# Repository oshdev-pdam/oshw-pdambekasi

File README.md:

# oshw-pdambekasi

Repositori rintisan untuk OSH Development sensor tekanan air untuk PDAM Kota Bekasi

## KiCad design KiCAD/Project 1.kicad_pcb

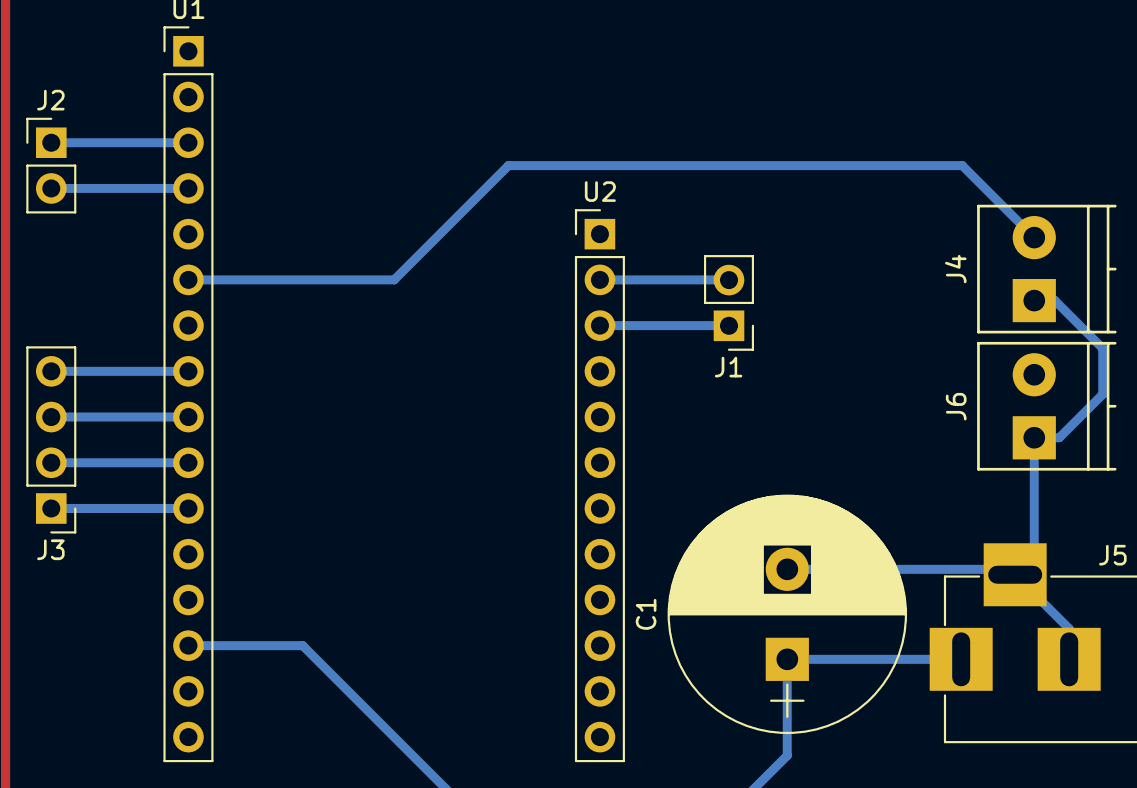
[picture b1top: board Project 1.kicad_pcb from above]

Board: 2 copper layers, 9 parts (0 on the bottom side), 11 nets.

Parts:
C1: CAP_POL; CP_Radial_D13.0mm_P5.00mm
J1: SIM900; Pin_Header_Straight_1x02_Pitch2.54mm
J2: RTC; Pin_Header_Straight_1x02_Pitch2.54mm
J3: Micro Pro; Pin_Header_Straight_1x04_Pitch2.54mm
J4: solid state controller; TerminalBlock_Phoenix_PT-3.5mm_2pol
J5: Jack-DC; BARREL_JACK
J6: Battery; TerminalBlock_Phoenix_PT-3.5mm_2pol
U1: ADAFRUIT_FEATHER; Pin_Header_Straight_1x16_Pitch2.54mm
U2: ADAFRUIT_FEATHER; Pin_Header_Straight_1x12_Pitch2.54mm

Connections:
DE: J3.2, U1.10
DI: J3.1, U1.11
GND: C1.2, J4.1, J5.2, J5.3, J6.1
RE: J3.3, U1.9
RO: J3.4, U1.8
RX: J1.2, U2.2
SCL: J2.2, U1.4
SDA: J2.1, U1.3
SS: J4.2, U1.6
TX: J1.1, U2.3
VCC: C1.1, J5.1, U1.14

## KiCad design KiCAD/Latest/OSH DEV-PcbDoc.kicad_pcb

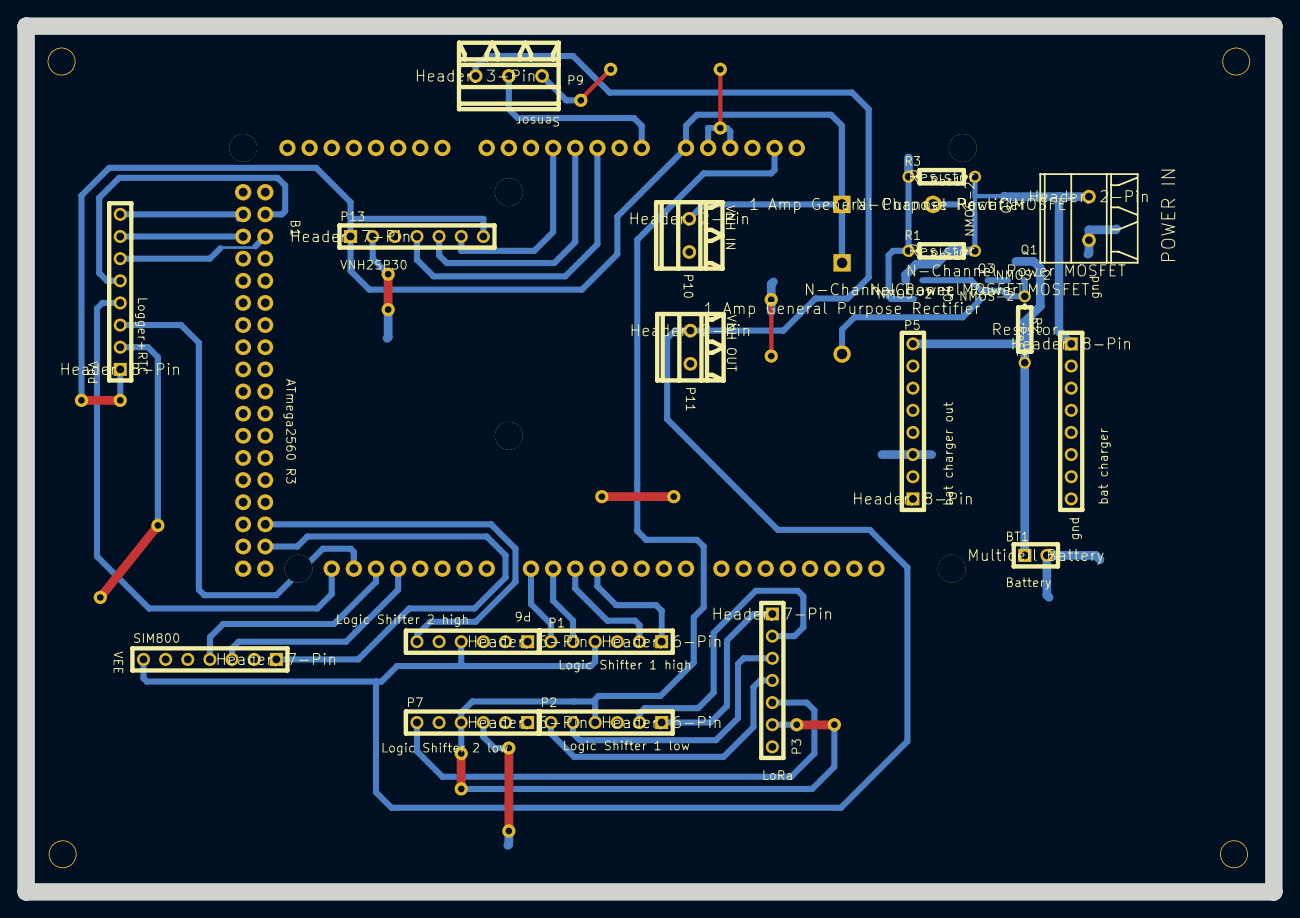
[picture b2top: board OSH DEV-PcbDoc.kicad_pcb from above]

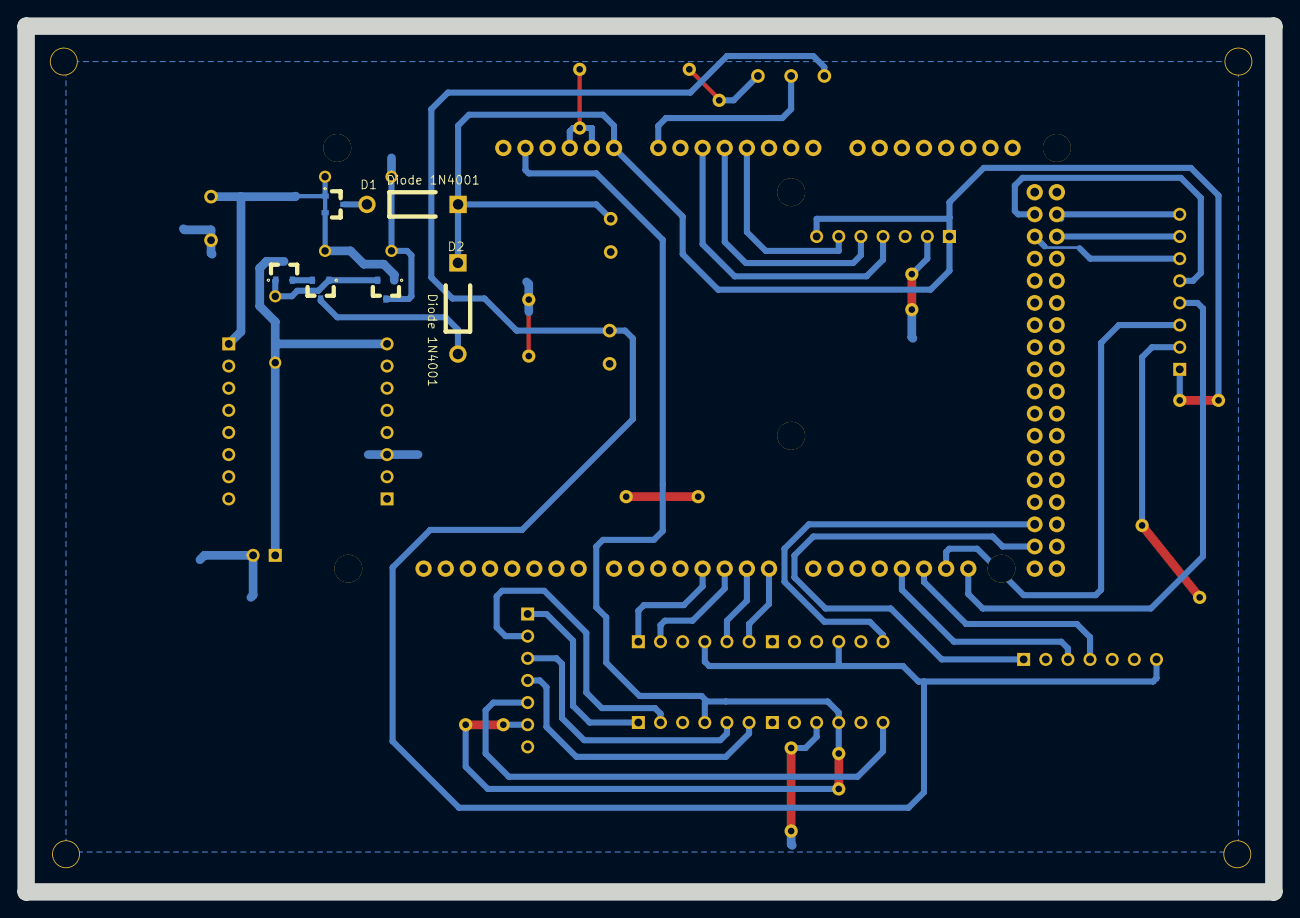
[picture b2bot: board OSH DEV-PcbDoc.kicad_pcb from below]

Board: 2 copper layers, 143.1 x 99.3 mm, 25 parts (6 on the bottom side), 33 nets.

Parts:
B1: ARDUINO_MEGA
BT1: Multicell Battery; BAT-2
D1, D2: 1 Amp General Purpose Rectifier; DO-41
P1, P2, P6, P7: Header, 6-Pin; HDR1X6
P3, P12, P13: Header, 7-Pin; HDR1X7
P4, P5, P14: Header, 8-Pin; HDR1X8
P8: Header, 2-Pin; MKDS3_2RMM
P9: Header, 3-Pin; MKDS1_3R3_8
P10, P11: Header, 2-Pin; MKDS1_2R3_8
Q1, Q2, Q3, Q4: N-Channel Power MOSFET; SOT-23B_L
R1, R2, R3: Resistor; AXIAL-0.3

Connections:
3.3: B1.3.3V, P2.4, P3.6, P7.4
GND: B1.GND@, BT1.2, P1.3, P2.3, P3.7, P4.6, P4.7, P4.8, P5.1, P5.2, P5.3, P6.3, P7.3, P8.2, P9.3, P10.2, P11.2, P12.6, P13.2, P14.2, Q4.3, R1.1, R3.1
NetB1_0: B1.0, P1.6
NetB1_1: B1.1, P1.5
NetB1_2: B1.2, P1.2
NetB1_3: B1.3, P1.1
NetB1_18: B1.18, P12.3
NetB1_19: B1.19, P12.4
NetB1_20: B1.20, P14.3
NetB1_21: B1.21, P14.4
NetB1_22: B1.22, P12.1
NetB1_24: B1.24, P6.6
NetB1_50: B1.50, P14.6
NetB1_51: B1.51, P14.7
NetB1_52: B1.52, P14.5
NetB1_53: B1.53, P14.8
NetB1_A0: B1.A0, P9.2
NetB1_A2: B1.A2, P13.4
NetB1_A3: B1.A3, P13.5
NetB1_A4: B1.A4, P13.6
NetD1_1: D1.1, Q2.3
NetD2_1: D2.1, Q3.3
NetP2_1: P2.1, P3.1
NetP2_2: P2.2, P3.2
NetP2_5: P2.5, P3.3
NetP2_6: P2.6, P3.4
NetP3_5: P3.5, P7.6
NetQ1_1: Q1.1, Q3.1, Q4.2, R2.1
NetQ1_2: Q1.2, Q3.2
VBAT: BT1.1, P5.8, Q1.3, R2.2
VDD: B1.VIN, D1.2, D2.2, P10.1, P13.1, P13.7, P14.1
VEE: P1.4, P6.4, P9.1, P11.1, P12.7
VIN: P4.1, P8.1, Q2.1, Q2.2, Q4.1, R1.2, R3.2

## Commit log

2017-10-12 Create Design
2017-10-12 reorganize repo
2017-10-12 merge
2017-10-17 Product Wireframe
    Representasi visual dari alur kerja alat, ditampilkan dalam dokumentasi secara deskriptif dan dengan bantuan berupa bagan
2017-10-19 Bill Of Material
    anggaran perbelanjaan dan link toko pembelian
2017-10-19 Add BOM Completion for Unit 1
2017-10-20 KiCAD files eeschema and pcb
2017-10-20 KiCAD
    KiCAD file seluruh design skematik (Eeschema) dan PCB
2017-10-20 KiCAD Files
    Eeschema dan PCB file electrical design
2017-10-30 KiCAD Files
    KiCAD files lengkap untuk design ver.1
2017-10-31 Basic Function Codes
    Master: Adafruit Feather M0
    Slave: Arduino Micro
2017-11-06 Full Code v1
2017-11-06 Conversion to VS2017 and add .gitignore
2017-11-19 Use FONA library with SIM800L
2017-12-28 2nd gen
    Code dev for 2nd generation module. No more slave
2018-01-17 Module v2 (Gateway)
2018-02-25 HTTP Data Send Update
    Now sending data through Adafruit.io's REST API
2018-02-25 Quota Check Update
    Added quota check, using USSD commands
2018-04-09 Latest PCB Design
2018-04-11 Latest Schematics
2018-04-12 Schematics PDF
2018-04-24 Data Gathering & Analysis
    Ambil data bulan Maret-April untuk unit 1, 2, 3. Program untuk mengkonversi data .json ke .csv (dan grafik penggunaan 24 jam) ada di file Data_Gathering.py
2018-07-15 v4
    Code with 10 minutes sleep time
2018-07-22 Sleep Upgrade
    Use proper internal sleep features
2018-07-31 v4 correction
2018-08-13 v5
    Cleaned up code
2018-08-31 PCB file Altium
    PCB file ini lebih umum digunakan untuk percetakan di rumah pembuatan PCB lokal. dengan mengirimkan file ini langsung ke rumah pembuatan PCB tidak sesulit mereka untuk memproses file PCB dari KiCAD
2018-09-25 Code ver. FINAL
